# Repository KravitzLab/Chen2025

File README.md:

# Chen2026
Data and analysis of Chen et al. (in submission)<br>
Preprint here: https://www.biorxiv.org/content/10.1101/2025.08.21.671364v2

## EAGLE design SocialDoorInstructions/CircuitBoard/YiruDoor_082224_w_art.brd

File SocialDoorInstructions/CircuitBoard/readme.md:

This folder contains the .sch and .brd files for producing the custom printed circuit board (PCB)

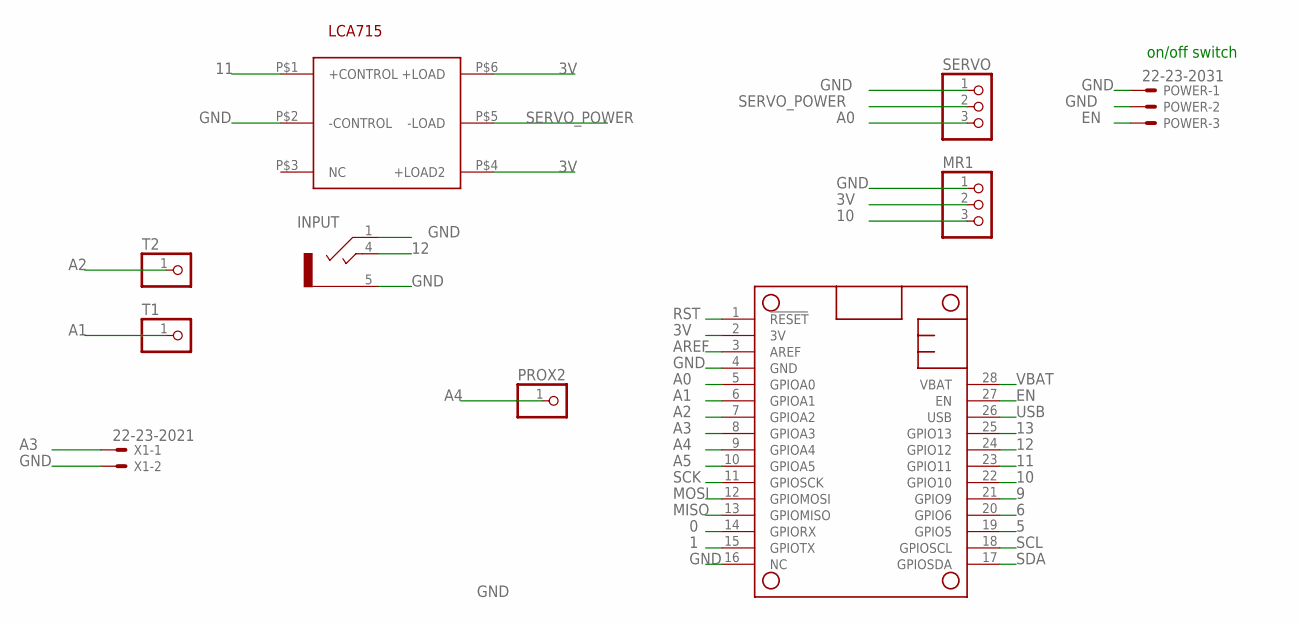
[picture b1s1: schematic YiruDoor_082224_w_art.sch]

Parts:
INPUT: STEREO_JACK; 35RASMT2BHNTRX
MR1: PINHD-1X3; 1X03
MS2: MICROSHIELD_NODIM; MICROSHIELD_DIM
POWER: 22-23-2031
PROX2: PINHD-1X1; 1X01
SERVO: PINHD-1X3; 1X03
SSR3: LCA715S; LCA7XX
T1, T2: PINHD-1X1; 1X01
X1: 22-23-2021

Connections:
0: MS2.14 (GPIORX)
1: MS2.15 (GPIOTX)
3V: MR1.2, MS2.2 (3V), SSR3.P$4 (+LOAD2), SSR3.P$6 (+LOAD)
5: MS2.19 (GPIO5)
6: MS2.20 (GPIO6)
9: MS2.21 (GPIO9)
10: MR1.3, MS2.22 (GPIO10)
11: MS2.23 (GPIO11), SSR3.P$1 (+CONTROL)
12: INPUT.4, MS2.24 (GPIO12)
13: MS2.25 (GPIO13)
A0: MS2.5 (GPIOA0), SERVO.3
A1: MS2.6 (GPIOA1), T1.1
A2: MS2.7 (GPIOA2), T2.1
A3: MS2.8 (GPIOA3), X1.1
A4: MS2.9 (GPIOA4), PROX2.1
A5: MS2.10 (GPIOA5)
AREF: MS2.3 (AREF)
EN: MS2.27 (EN), POWER.3
GND: INPUT.1, INPUT.5, MR1.1, MS2.4 (GND), MS2.16 (NC), POWER.1, POWER.2, SERVO.1, SSR3.P$2 (-CONTROL), X1.2
MISO: MS2.13 (GPIOMISO)
MOSI: MS2.12 (GPIOMOSI)
RST: MS2.1 (!RESET)
SCK: MS2.11 (GPIOSCK)
SCL: MS2.18 (GPIOSCL)
SDA: MS2.17 (GPIOSDA)
SERVO_POWER: SERVO.2, SSR3.P$5 (-LOAD)
USB: MS2.26 (USB)
VBAT: MS2.28 (VBAT)

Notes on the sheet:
on/off switch

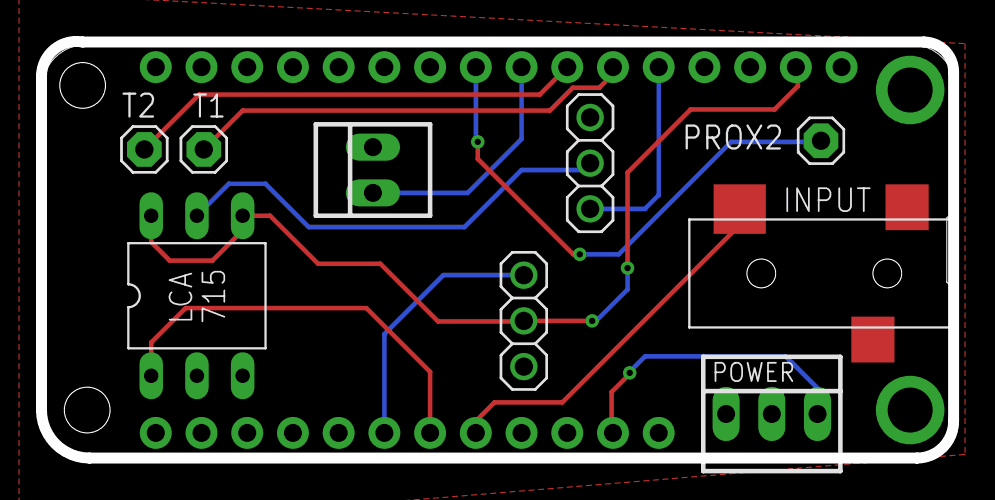
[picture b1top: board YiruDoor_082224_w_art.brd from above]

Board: 2 copper layers, 50.7 x 23.1 mm, 10 parts (0 on the bottom side), 12 nets.

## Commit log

2025-06-23 Edited figure
2025-06-23 Uploaded data
2025-06-23 Created using Colab
2025-06-23 Moved file
2025-06-24 Updated datafiles
2025-06-25 Updated using Colab
2025-07-01 Updated images
2025-07-01 Updated data
2025-07-10 Uploaded video
2025-07-18 Updated data & code
2025-07-31 Updated figures
2025-07-31 Updated code
2025-08-05 Add Social Door Arduino v1.0 source files
    Initial commit of the Social Door v1.0 Arduino codebase, including battery monitoring, display management, sensor reading, SD card logging, door control logic, device configuration, I2C setup, and st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
2025-08-05 Add Social Door Arduino and PCB source files
    Initial commit of SocialDoor_Touch_080525 Arduino code, including battery, display, sensor, logging, and door control modules, as well as header and startup logic. Also adds YiruDoor_082224_w_art boa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
2025-08-05 Add touch sensor baseline tracking and troubleshooting
    Introduced baseline tracking for touch sensors in SocialDoor Arduino code, including periodic updates and pulse detection logic. Added Timeout utility and a new troubleshooting sketch for touch senso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
2025-08-05 Integrate Adafruit_FreeTouch sensors for touch input
    Replaced placeholder touch sensor objects with Adafruit_FreeTouch instances for left and right sensors. Updated baseline calculation and logging for improved sensor stability. Added sensor initializa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
2025-08-05 Add touch duration logic for sensor activation
    Introduces variables and logic to require a minimum touch duration before triggering door actions for both left and right sensors. This helps prevent accidental activations by ensuring touches must l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
2025-08-06 Refactor touch logic and improve logging in Social Door
    Moved touch sensor logic to a new Touch.ino file and button logic to Buttons.ino for better modularity. Updated event counting to use 'event' instead of 'open_num' throughout the code. Enhanced data 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
2025-08-19 Updated files
2025-08-20 Updated videos
2025-08-21 Added figures
2025-08-21 Updated video names
2025-08-21 Clean up Arduino code and fix video filename typo
    Removed commented-out and unused code from OpenDoor.ino for better readability and maintainability. Also corrected a typo in the video filename, renaming 'Movei 2. Nonreciprocal interaction.mp4' to '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
2025-08-21 Replace .mp4 videos with .m4v versions
    Removed .mp4 video files and added corresponding .m4v versions for all five interaction movies in the Videos directory. This may be for format standardization or compatibility reasons.
2026-01-12 Updated dataset
2026-01-12 Update all main and supplementary figure images
    Replaced Figures 1-5 and Supplementary Figures S1-S5 with updated versions. This likely reflects new data, improved image quality, or corrections to the figures.
2026-01-14 Update project title and submission status
2026-01-20 Move doordata_process.ipynb to new directory
    Renamed and relocated doordata_process.ipynb to the SocialDoorInstructions directory for better project organization.
2026-04-06 Add routing image to circuit board readme
